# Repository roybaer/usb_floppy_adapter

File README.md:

# USB to Floppy-Disk Drive Adapter

This project provides the CAD files for an STM32-based floppy-disk controller that can be attached to the back of an ordinary 3.5 inch floppy-disk drive and connected to a USB host via micro USB port.

## Hardware

The core of this adapter is the popular STM32F103C8T6 microcontroller by STMicroelectronics.
Please consult the [PDF schematic](schematic.pdf) for details.

### Configuration

The adapter can be used in several different hardware configurations that can be selected via solder bridges.

The following drive types are supported:

- PC drives
- IBM PS/2 drives
- drives with shugart interface

Drives that only use the 5V line and consume less than approx. 480mA can be powered via USB, other drives have to be powered externally.

J5    | J6    | J7       | Use case
------|-------|----------|---------
▒▒░▒▒ | ▒▒░▒▒ | ▒▒░▒▒░▒▒ | PC drive, externally powered
▓▓▓▓▓ | ▒▒░▒▒ | ▒▒░▒▒░▒▒ | IBM PS/2 drive without 12V line
▒▒░▒▒ | ▓▓▓▓▓ | ▒▒░▒▒░▒▒ | PC drive, USB-powered
▒▒░▒▒ | ▒▒░▒▒ | ▓▓▓▓▓░▒▒ | pin 4 and 6 shorted, for shugart drives that do not use pin 4
▒▒░▒▒ | ▒▒░▒▒ | ▒▒░▓▓▓▓▓ | 12V on pin 4, for PS/2 drive

The power connector J3 can be used as either input or output.

Configurations other than the USB-powered PC drive (see [picture](img/pc_drive.jpg)) are untested.

## Firmware

As of August 2020, there is no working firmware for this adapter, yet.

The objective is to adapt the firmware provided by the [Greaseweazle project](https://github.com/keirf/Greaseweazle).
It does already provide support for the same microcontroller, albeit for a much bulkier adapter with a different pinout.

### Programming via Serial Wire Debug Interface

The adapter provides solder pads for an SWD programming device. They are labeled J4 on the PCB.

Pin on J4 | Function
----------|---------
1 | 3.3V
2 | SWDIO
3 | SWCLK
4 | GND

## Software

Please refer to the Greaseweazle documentation for PC-side software that will be used with this adapter.

## License

The following license applies to the files in this repository:

This work is licensed under the Creative Commons Attribution-ShareAlike 4.0 International License. To view a copy of this license, visit http://creativecommons.org/licenses/by-sa/4.0/ or send a letter to Creative Commons, PO Box 1866, Mountain View, CA 94042, USA.

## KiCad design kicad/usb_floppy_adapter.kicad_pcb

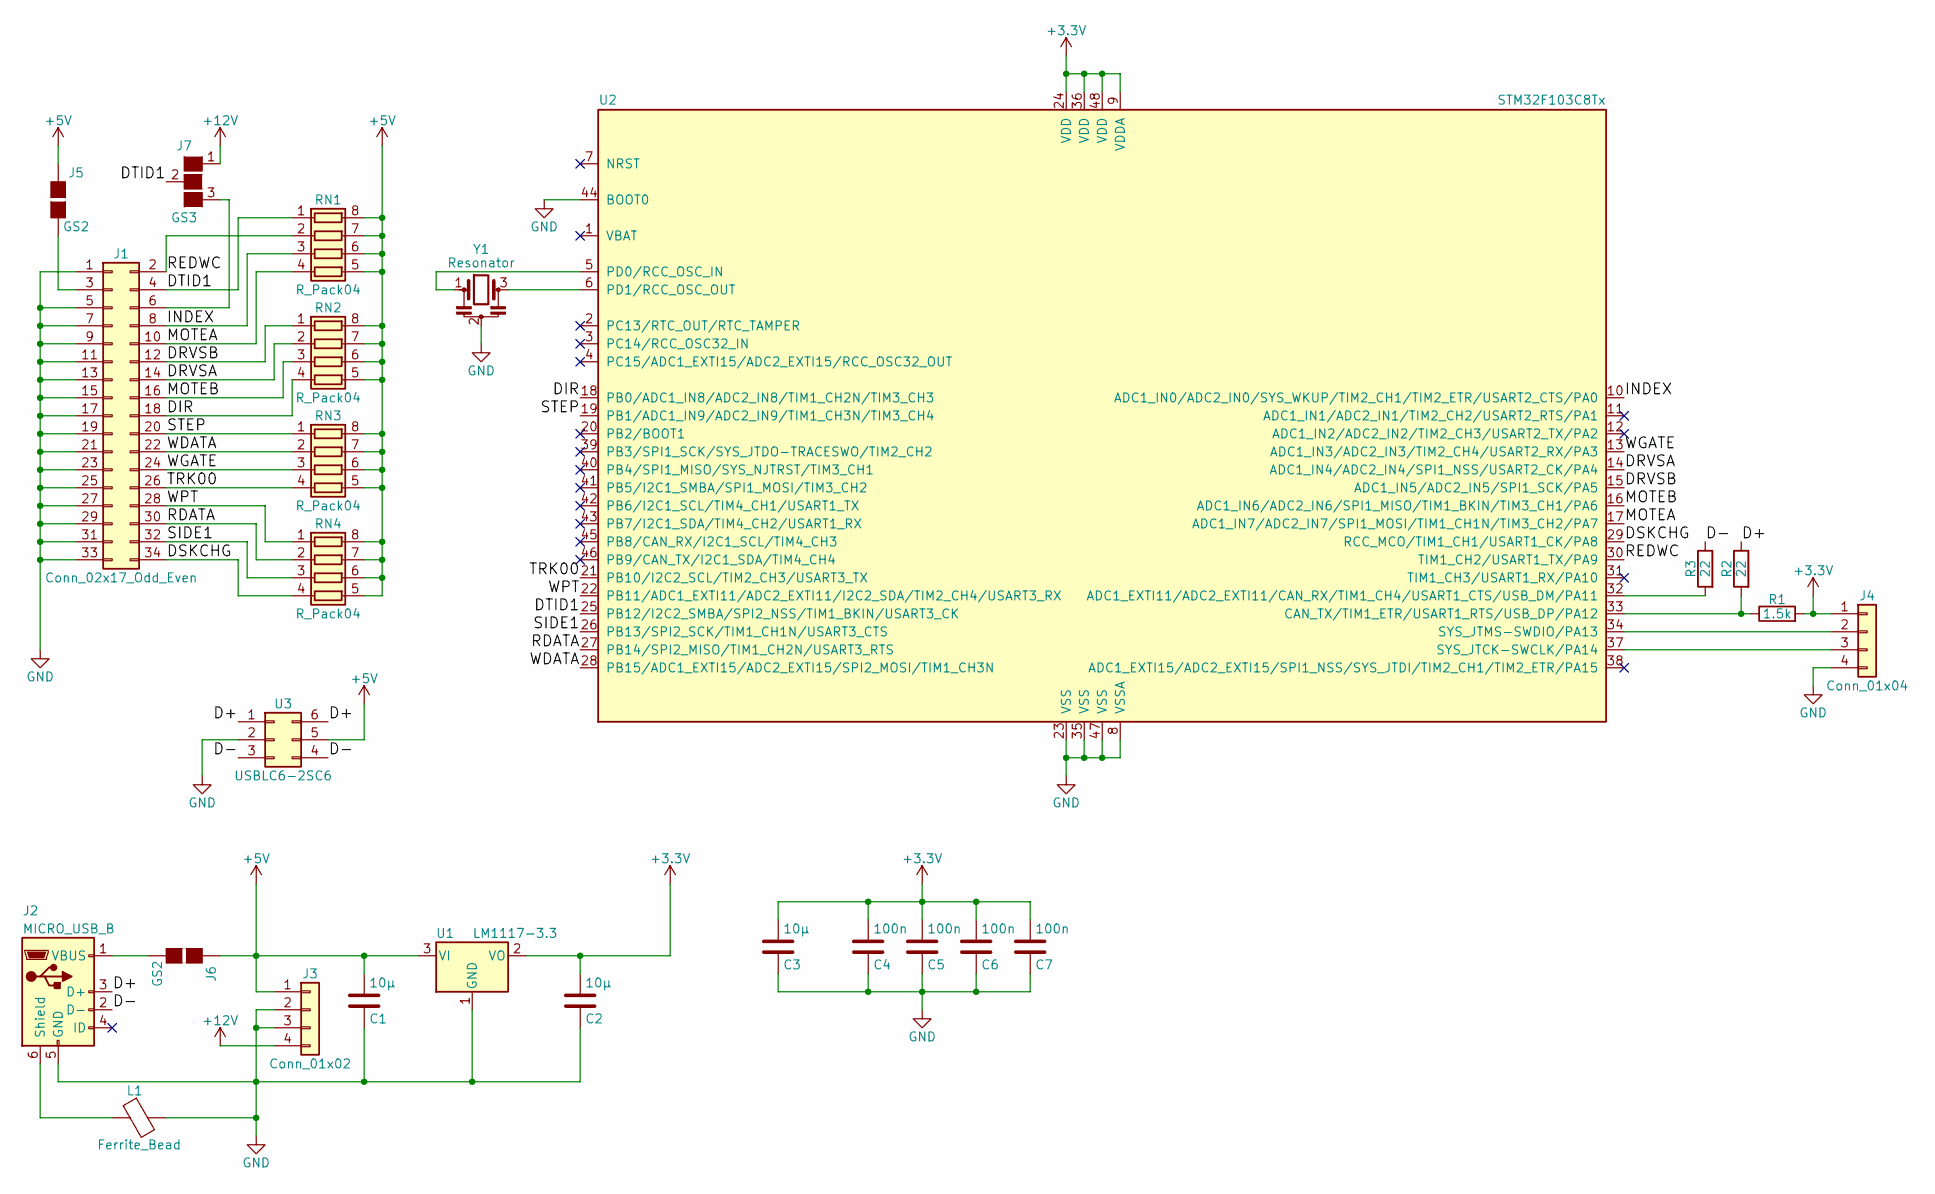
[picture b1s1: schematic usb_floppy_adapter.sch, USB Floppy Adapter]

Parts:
C1, C2, C3: 10µ; C_0805
C4, C5, C6, C7: 100n; C_0603
J1: Conn_02x17_Odd_Even; Socket_Strip_Straight_2x17_Pitch2.54mm
J2: MICRO_USB_B; USB_Micro-B_Vertical_Molex-105133-0001
J3: Conn_01x02; Pin_Header_Straight_1x04_Pitch2.54mm
J4: Conn_01x04; Pin_Header_Straight_1x04_Pitch1.27mm_SMD_Pin1Left
J5, J6: GS2
J7: GS3
L1: Ferrite_Bead; L_0805
R1: 1.5k; R_0603
R2, R3: 22; R_0603
RN1, RN2, RN3, RN4: R_Pack04; R_Array_Convex_4x0603
U1: LM1117-3.3; SOT-223-3Lead_TabPin2
U2: STM32F103C8Tx; LQFP-48_7x7mm_Pitch0.5mm
U3: USBLC6-2SC6; SOT-23-6
Y1: Resonator; Resonator_SMD_muRata_SFECV-3pin_6.9x2.9mm

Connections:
+3V3: C2.2, C3.2, C4.2, C5.2, C6.2, C7.2, J4.1, R1.2, U1.2 (VO), U2.9 (VDDA), U2.24 (VDD), U2.36 (VDD), U2.48 (VDD)
+5V: C1.2, J3.1, J5.1 (G1), J6.1 (G1), RN1.5 (R4.2), RN1.6 (R3.2), RN1.7 (R2.2), RN1.8 (R1.2), RN2.5 (R4.2), RN2.6 (R3.2), RN2.7 (R2.2), RN2.8 (R1.2), RN3.5 (R4.2), RN3.6 (R3.2), RN3.7 (R2.2), RN3.8 (R1.2), RN4.5 (R4.2), RN4.6 (R3.2), RN4.7 (R2.2), RN4.8 (R1.2), U1.3 (VI), U3.5
+12V: J3.4, J7.1 (G1)
/D+: J2.3 (D+), R2.1, U3.1, U3.6
/D-: J2.2 (D-), R3.1, U3.3, U3.4
/DIR: J1.18, RN2.4 (R4.1), U2.18 (PB0/ADC1_IN8/ADC2_IN8/TIM1_CH2N/TIM3_CH3)
/DRVSA: J1.14, RN2.2 (R2.1), U2.14 (ADC1_IN4/ADC2_IN4/SPI1_NSS/USART2_CK/PA4)
/DRVSB: J1.12, RN2.1 (R1.1), U2.15 (ADC1_IN5/ADC2_IN5/SPI1_SCK/PA5)
/DSKCHG: J1.34, RN4.4 (R4.1), U2.29 (RCC_MCO/TIM1_CH1/USART1_CK/PA8)
/DTID1: J1.4, J7.2 (G2), RN1.1 (R1.1), U2.25 (PB12/I2C2_SMBA/SPI2_NSS/TIM1_BKIN/USART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)
/INDEX: J1.8, RN1.3 (R3.1), U2.10 (ADC1_IN0/ADC2_IN0/SYS_WKUP/TIM2_CH1/TIM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)
/MOTEA: J1.10, RN1.4 (R4.1), U2.17 (ADC1_IN7/ADC2_IN7/SPI1_MOSI/TIM1_CH1N/T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)
/MOTEB: J1.16, RN2.3 (R3.1), U2.16 (ADC1_IN6/ADC2_IN6/SPI1_MISO/TIM1_BKIN/T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)
/RDATA: J1.30, RN4.2 (R2.1), U2.27 (PB14/SPI2_MISO/TIM1_CH2N/USART3_RTS)
/REDWC: J1.2, RN1.2 (R2.1), U2.30 (TIM1_CH2/USART1_TX/PA9)
/SIDE1: J1.32, RN4.3 (R3.1), U2.26 (PB13/SPI2_SCK/TIM1_CH1N/USART3_CTS)
/STEP: J1.20, RN3.1 (R1.1), U2.19 (PB1/ADC1_IN9/ADC2_IN9/TIM1_CH3N/TIM3_CH4)
/TRK00: J1.26, RN3.4 (R4.1), U2.21 (PB10/I2C2_SCL/TIM2_CH3/USART3_TX)
/WDATA: J1.22, RN3.2 (R2.1), U2.28 (PB15/ADC1_EXTI15/ADC2_EXTI15/SPI2_MOSI/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)
/WGATE: J1.24, RN3.3 (R3.1), U2.13 (ADC1_IN3/ADC2_IN3/TIM2_CH4/USART2_RX/PA3)
/WPT: J1.28, RN4.1 (R1.1), U2.22 (PB11/ADC1_EXTI11/ADC2_EXTI11/I2C2_SDA/T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)
GND: C1.1, C2.1, C3.1, C4.1, C5.1, C6.1, C7.1, J1.1, J1.5, J1.7, J1.9, J1.11, J1.13, J1.15, J1.17, J1.19, J1.21, J1.23, J1.25, J1.27, J1.29, J1.31, J1.33, J2.5 (GND), J3.2, J3.3, J4.4, L1.2, U1.1 (GND), U2.8 (VSSA), U2.23 (VSS), U2.35 (VSS), U2.44 (BOOT0), U2.47 (VSS), U3.2, Y1.2
unnamed: J1.3, J5.2 (G2)
unnamed: J1.6, J7.3 (G3)
unnamed: J2.1 (VBUS), J6.2 (G2)
unnamed: J2.6 (Shield), L1.1
unnamed: J4.2, U2.34 (SYS_JTMS-SWDIO/PA13)
unnamed: J4.3, U2.37 (SYS_JTCK-SWCLK/PA14)
unnamed: R1.1, R2.2, U2.33 (CAN_TX/TIM1_ETR/USART1_RTS/USB_DP/PA12)
unnamed: R3.2, U2.32 (ADC1_EXTI11/ADC2_EXTI11/CAN_RX/TIM1_CH4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)
unnamed: U2.5 (PD0/RCC_OSC_IN), Y1.1
unnamed: U2.6 (PD1/RCC_OSC_OUT), Y1.3

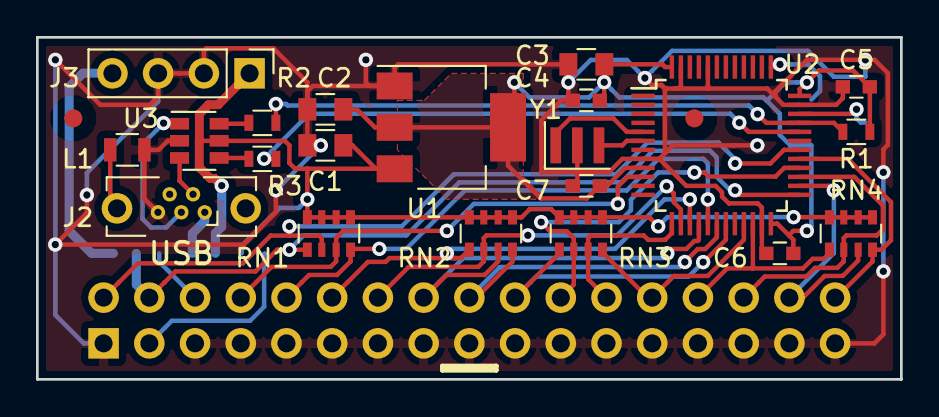
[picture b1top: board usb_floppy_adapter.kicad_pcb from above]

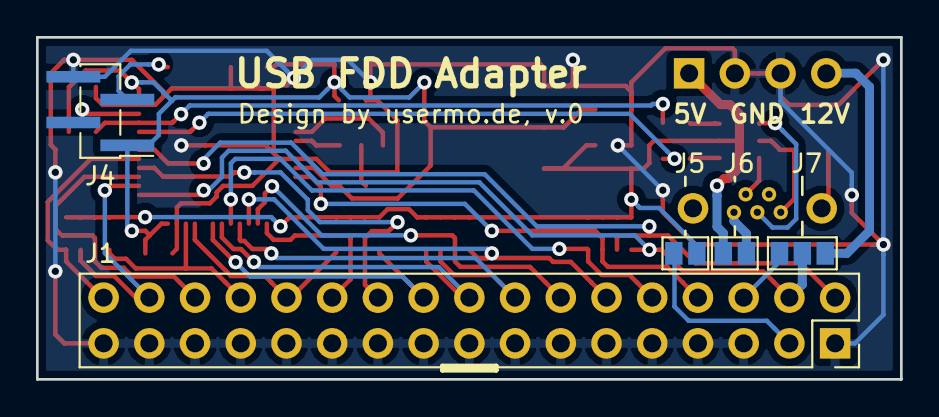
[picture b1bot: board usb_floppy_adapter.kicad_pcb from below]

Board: 2 copper layers, 48.0 x 19.0 mm, 26 parts (5 on the bottom side), 32 nets.

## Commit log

2018-02-04 add termination resistors
2018-02-08 silk screen
2018-02-08 set board thickness to 1.2mm
2018-02-19 add README.md
2018-03-03 Preparations for first prototype run
    - Tie BOOT0 to GND to ensure proper boot-up
    - Mark all unused MCU pins in the schematic as N/C
    - Double the width of the most important 5V and 12V traces
    - Move some traces further away from pads
    - Optimize parameters of Copper Fills
    - Add meta data and revision number (revision 0)
2018-05-05 add picture
2020-08-22 update documentation and pictures
2020-09-16 add missing word
